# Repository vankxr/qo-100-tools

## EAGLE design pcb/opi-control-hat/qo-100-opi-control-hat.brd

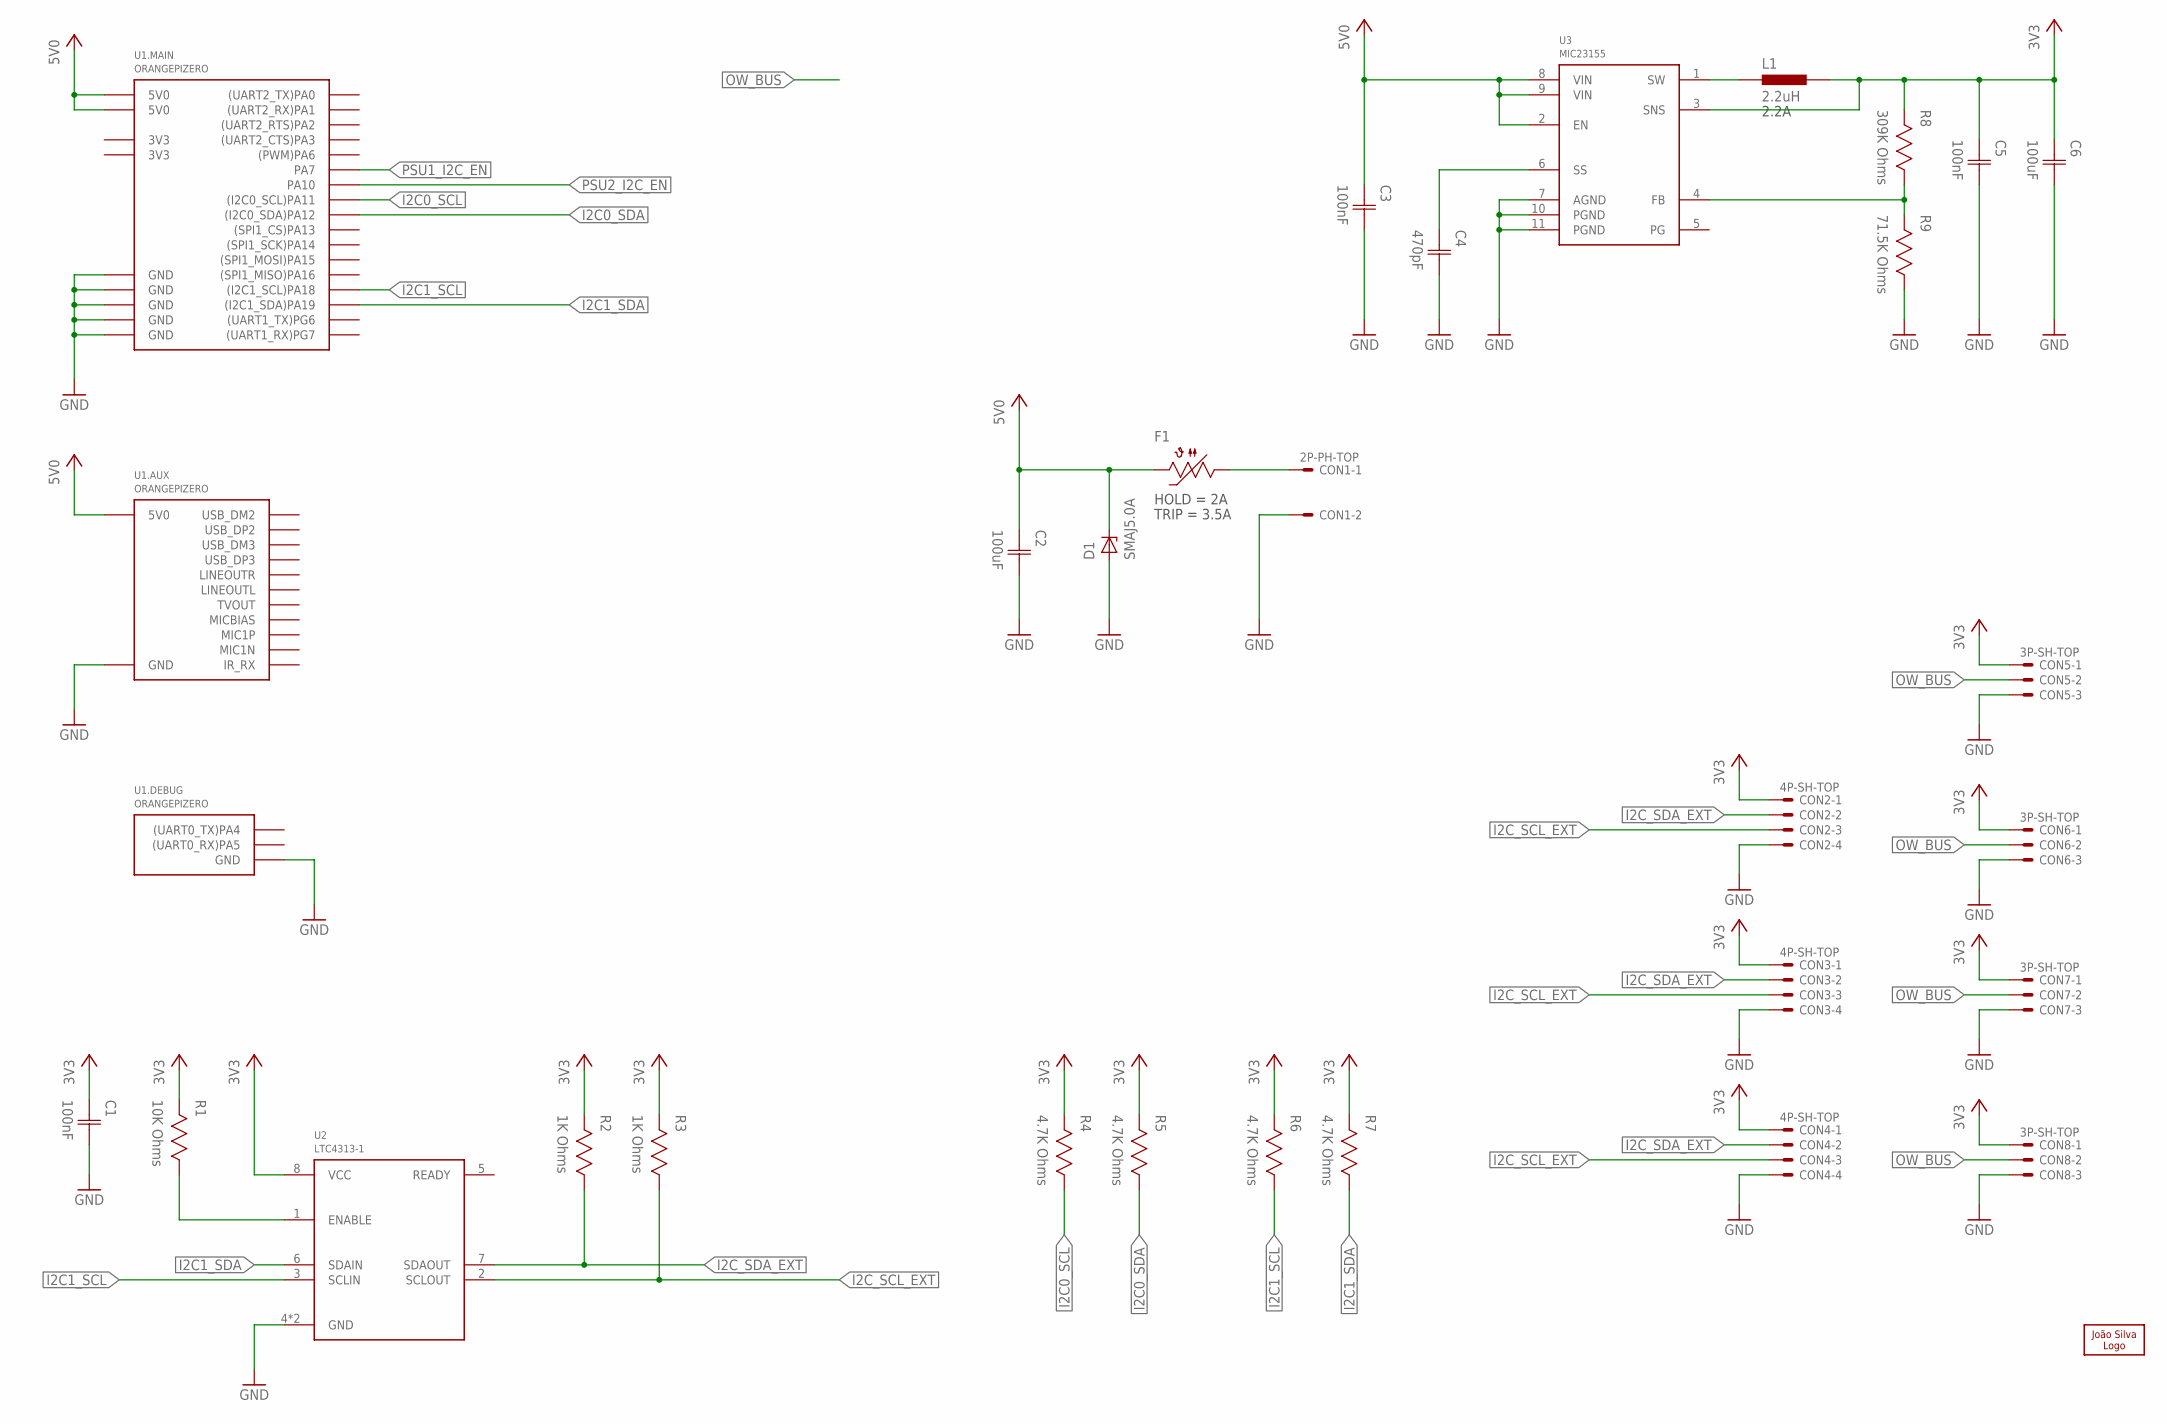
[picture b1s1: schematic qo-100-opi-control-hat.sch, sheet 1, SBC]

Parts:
C1, C3, C5: 100nF; CAP0603
C2, C6: 100uF; CAP1206
C4: 470pF; CAP0603
CON1: 2P-PH-TOP; PH-02-TOP
CON2, CON3, CON4: 4P-SH-TOP; SH-04-TOP
CON5, CON6, CON7, CON8: 3P-SH-TOP; SH-03-TOP
D1: SMAJ5.0A; DO214AC
F1: PTC1206; 1206
L1: 2.2uH; IND2520
LOGO1: JS-5MM; JS_5MM
R1: 10K Ohms; RES0603
R2, R3: 1K Ohms; RES0603
R4, R5, R6, R7: 4.7K Ohms; RES0603
R8: 309K Ohms; RES0603
R9: 71.5K Ohms; RES0603
U1: ORANGEPIZERO
U2: LTC4313-1; DFN8
U3: MIC23155; DFN10

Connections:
3V3: C1.1 (C1), C5.1 (C1), C6.1 (C1), CON2.1, CON3.1, CON4.1, CON5.1, CON6.1, CON7.1, CON8.1, L1.2, R1.2, R2.2, R3.2, R4.2, R5.2, R6.2, R7.2, R8.2, U2.8 (VCC), U3.3 (SNS); also elsewhere on the board
3V3_FB: R8.1, R9.2, U3.4 (FB)
3V3_SOFTSTART: C4.1 (C1), U3.6 (SS)
3V3_SW: L1.1, U3.1 (SW)
5V0: C2.1 (C1), C3.1 (C1), D1.C, F1.2, U1.MH$2 (5V0), U1.MH$4 (5V0), U1.SH$1 (5V0), U3.2 (EN), U3.8 (VIN), U3.9 (VIN)
GND: C1.2 (C2), C2.2 (C2), C3.2 (C2), C4.2 (C2), C5.2 (C2), C6.2 (C2), CON1.2, CON2.4, CON3.4, CON4.4, CON5.3, CON6.3, CON7.3, CON8.3, D1.A, R9.1, U1.DBG$1 (GND), U1.MH$6 (GND), U1.MH$9 (GND), U1.MH$14 (GND), U1.MH$20 (GND), U1.MH$25 (GND), U1.SH$2 (GND), U2.4 (GND), U2.9 (GND), U3.7 (AGND), U3.10 (PGND), U3.11 (PGND); also elsewhere on the board
I2C0_SCL: R4.1, U1.MH$5 ((I2C0_SCL)PA11); also elsewhere on the board
I2C0_SDA: R5.1, U1.MH$3 ((I2C0_SDA)PA12); also elsewhere on the board
I2C1_SCL: R6.1, U1.MH$18 ((I2C1_SCL)PA18), U2.3 (SCLIN)
I2C1_SDA: R7.1, U1.MH$16 ((I2C1_SDA)PA19), U2.6 (SDAIN)
I2C_SCL_EXT: CON2.3, CON3.3, CON4.3, R3.1, U2.2 (SCLOUT)
I2C_SDA_EXT: CON2.2, CON3.2, CON4.2, R2.1, U2.7 (SDAOUT)
unnamed: CON1.1, F1.1
unnamed: R1.1, U2.1 (ENABLE)
OW_BUS: CON5.2, CON6.2, CON7.2, CON8.2
PSU1_I2C_EN: U1.MH$12 (PA7); also elsewhere on the board
PSU2_I2C_EN: U1.MH$26 (PA10); also elsewhere on the board

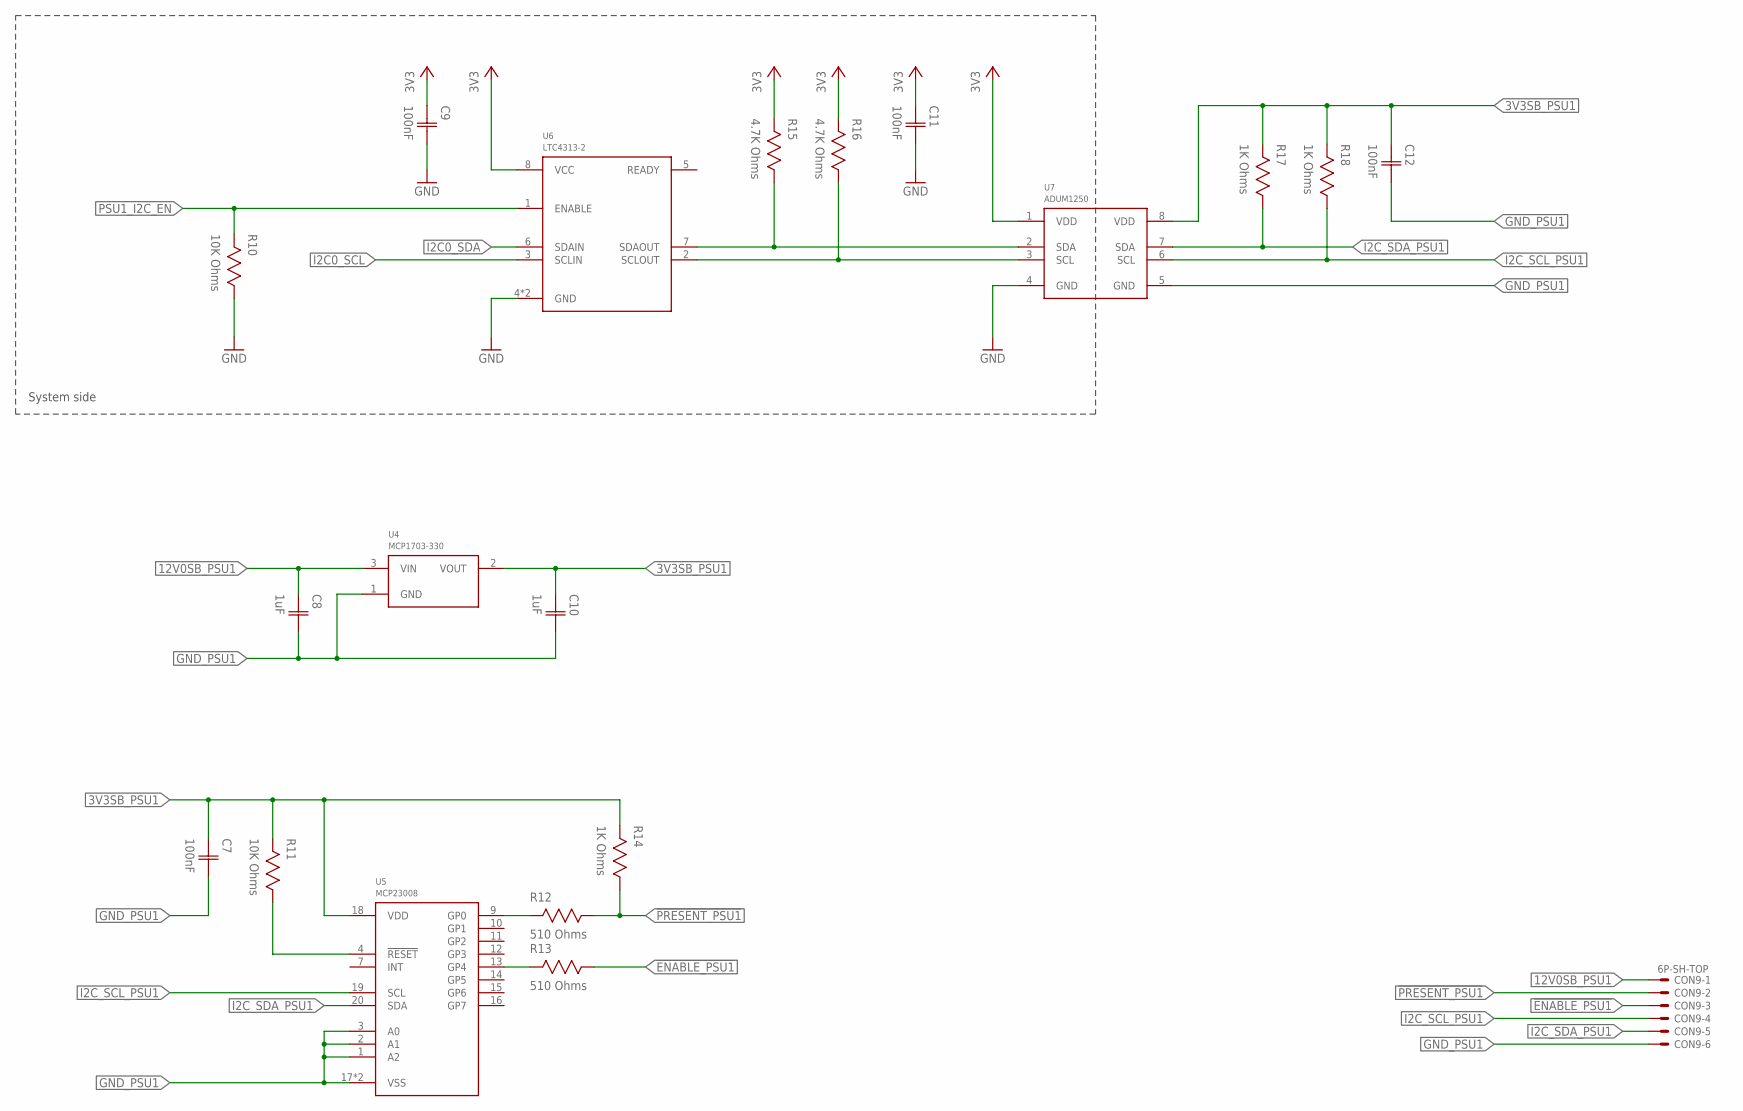
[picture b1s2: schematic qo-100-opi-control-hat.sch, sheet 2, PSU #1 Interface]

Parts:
C7, C9, C11, C12: 100nF; CAP0603
C8, C10: 1uF; CAP0603
CON9: 6P-SH-TOP; SH-06-TOP
R10, R11: 10K Ohms; RES0603
R12, R13: 510 Ohms; RES0603
R14, R17, R18: 1K Ohms; RES0603
R15, R16: 4.7K Ohms; RES0603
U4: MCP1703-330; SOT23
U5: MCP23008; QFN20
U6: LTC4313-2; DFN8
U7: ADUM1250; SOIC8

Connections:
3V3: C9.1 (C1), C11.1 (C1), R15.2, R16.2, U6.8 (VCC), U7.1 (VDD); also elsewhere on the board
3V3SB_PSU1: C7.1 (C1), C10.1 (C1), C12.1 (C1), R11.2, R14.2, R17.2, R18.2, U4.2 (VOUT), U5.18 (VDD), U7.8 (VDD)
12V0SB_PSU1: C8.1 (C1), CON9.1, U4.3 (VIN)
!ENABLE_PSU1: CON9.3, R13.1
!PRESENT_PSU1: CON9.2, R12.1, R14.1
GND: C9.2 (C2), C11.2 (C2), R10.1, U6.4 (GND), U6.9 (GND), U7.4 (GND); also elsewhere on the board
GND_PSU1: C7.2 (C2), C8.2 (C2), C10.2 (C2), C12.2 (C2), CON9.6, U4.1 (GND), U5.1 (A2), U5.2 (A1), U5.3 (A0), U5.17 (VSS), U5.PAD (VSS), U7.5 (GND)
I2C0_SCL: U6.3 (SCLIN); also elsewhere on the board
I2C0_SDA: U6.6 (SDAIN); also elsewhere on the board
I2C_SCL_PSU1: CON9.4, R18.1, U5.19 (SCL), U7.6 (SCL)
I2C_SDA_PSU1: CON9.5, R17.1, U5.20 (SDA), U7.7 (SDA)
unnamed: R16.1, U6.2 (SCLOUT), U7.3 (SCL)
unnamed: R15.1, U6.7 (SDAOUT), U7.2 (SDA)
unnamed: R11.1, U5.4 (!RESET)
unnamed: R13.2, U5.13 (GP4)
unnamed: R12.2, U5.9 (GP0)
PSU1_I2C_EN: R10.2, U6.1 (ENABLE); also elsewhere on the board

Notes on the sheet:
System side

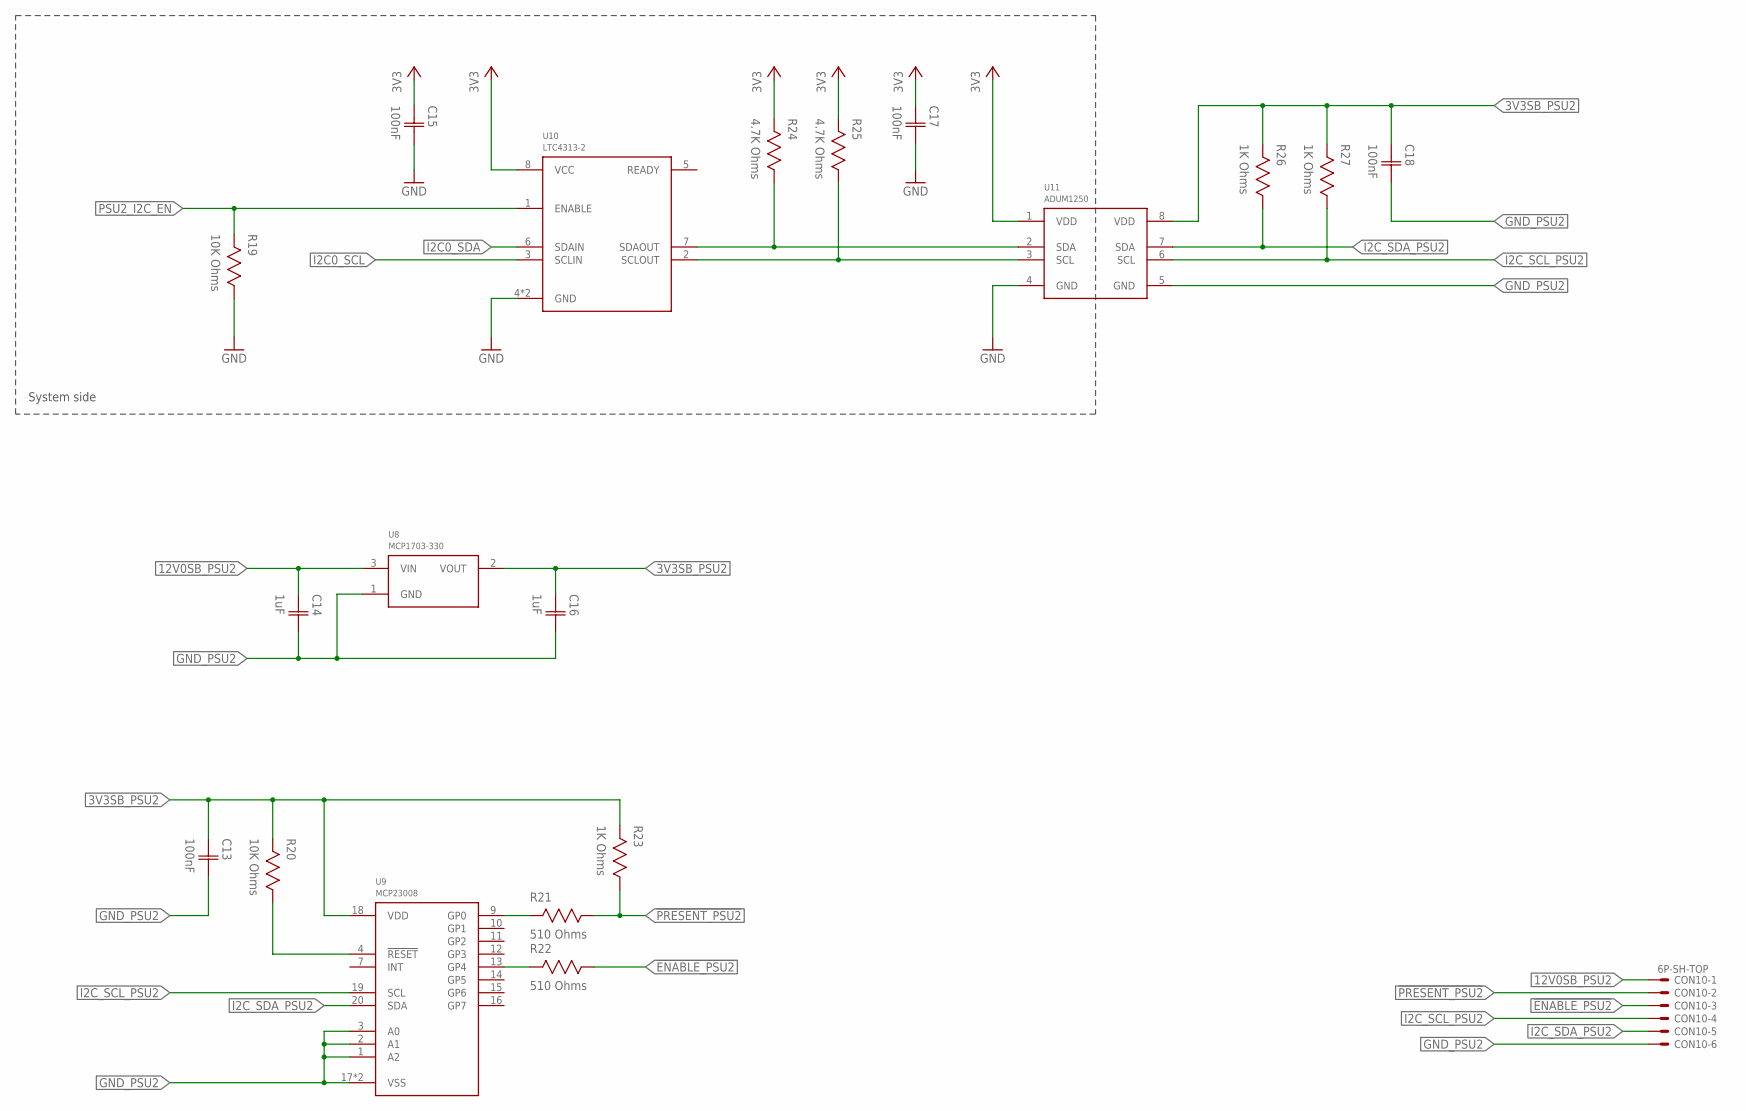
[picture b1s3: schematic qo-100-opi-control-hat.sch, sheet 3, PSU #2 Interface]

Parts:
C13, C15, C17, C18: 100nF; CAP0603
C14, C16: 1uF; CAP0603
CON10: 6P-SH-TOP; SH-06-TOP
R19, R20: 10K Ohms; RES0603
R21, R22: 510 Ohms; RES0603
R23, R26, R27: 1K Ohms; RES0603
R24, R25: 4.7K Ohms; RES0603
U8: MCP1703-330; SOT23
U9: MCP23008; QFN20
U10: LTC4313-2; DFN8
U11: ADUM1250; SOIC8

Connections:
3V3: C15.1 (C1), C17.1 (C1), R24.2, R25.2, U10.8 (VCC), U11.1 (VDD); also elsewhere on the board
3V3SB_PSU2: C13.1 (C1), C16.1 (C1), C18.1 (C1), R20.2, R23.2, R26.2, R27.2, U8.2 (VOUT), U9.18 (VDD), U11.8 (VDD)
12V0SB_PSU2: C14.1 (C1), CON10.1, U8.3 (VIN)
!ENABLE_PSU2: CON10.3, R22.1
!PRESENT_PSU2: CON10.2, R21.1, R23.1
GND: C15.2 (C2), C17.2 (C2), R19.1, U10.4 (GND), U10.9 (GND), U11.4 (GND); also elsewhere on the board
GND_PSU2: C13.2 (C2), C14.2 (C2), C16.2 (C2), C18.2 (C2), CON10.6, U8.1 (GND), U9.1 (A2), U9.2 (A1), U9.3 (A0), U9.17 (VSS), U9.PAD (VSS), U11.5 (GND)
I2C0_SCL: U10.3 (SCLIN); also elsewhere on the board
I2C0_SDA: U10.6 (SDAIN); also elsewhere on the board
I2C_SCL_PSU2: CON10.4, R27.1, U9.19 (SCL), U11.6 (SCL)
I2C_SDA_PSU2: CON10.5, R26.1, U9.20 (SDA), U11.7 (SDA)
unnamed: R25.1, U10.2 (SCLOUT), U11.3 (SCL)
unnamed: R24.1, U10.7 (SDAOUT), U11.2 (SDA)
unnamed: R20.1, U9.4 (!RESET)
unnamed: R22.2, U9.13 (GP4)
unnamed: R21.2, U9.9 (GP0)
PSU2_I2C_EN: R19.2, U10.1 (ENABLE); also elsewhere on the board

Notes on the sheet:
System side

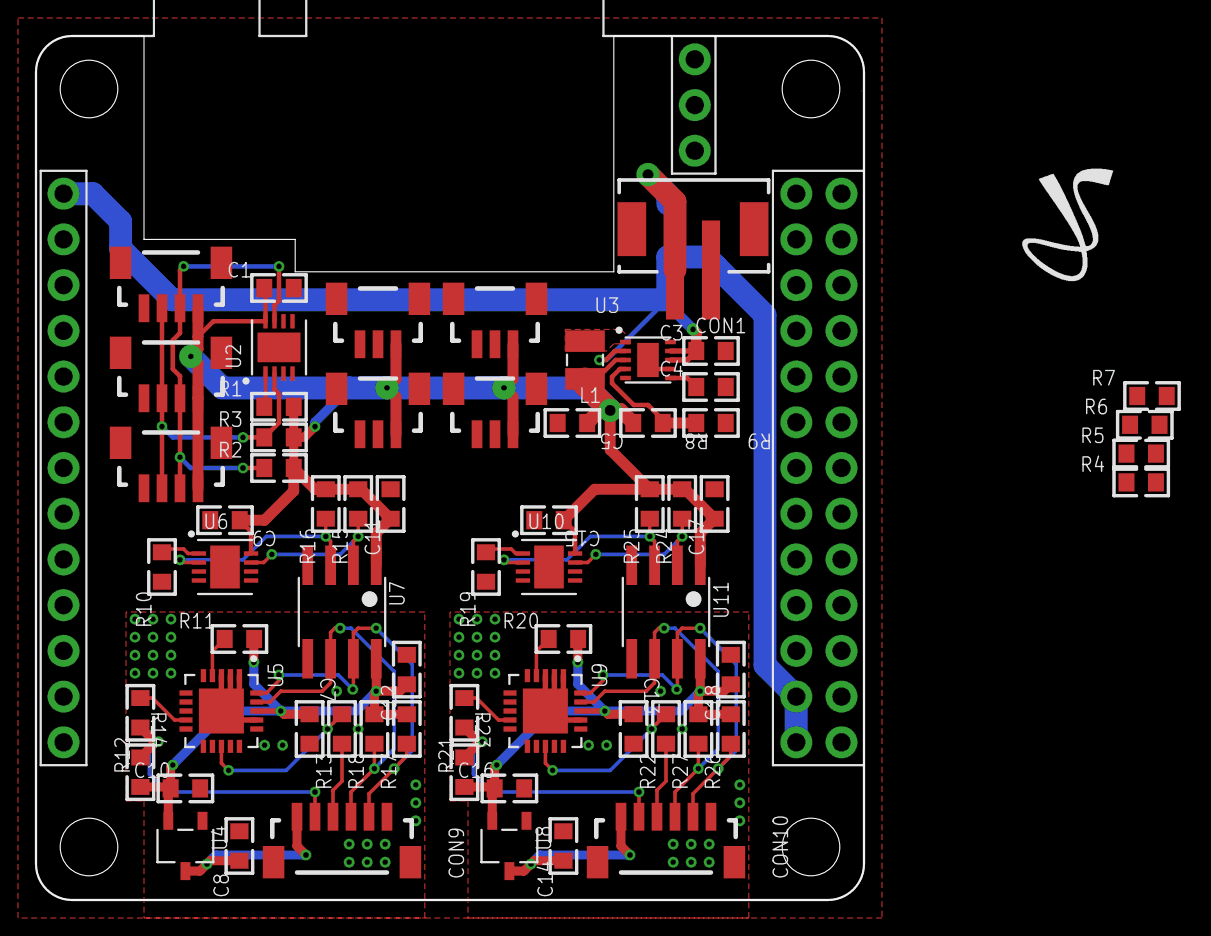
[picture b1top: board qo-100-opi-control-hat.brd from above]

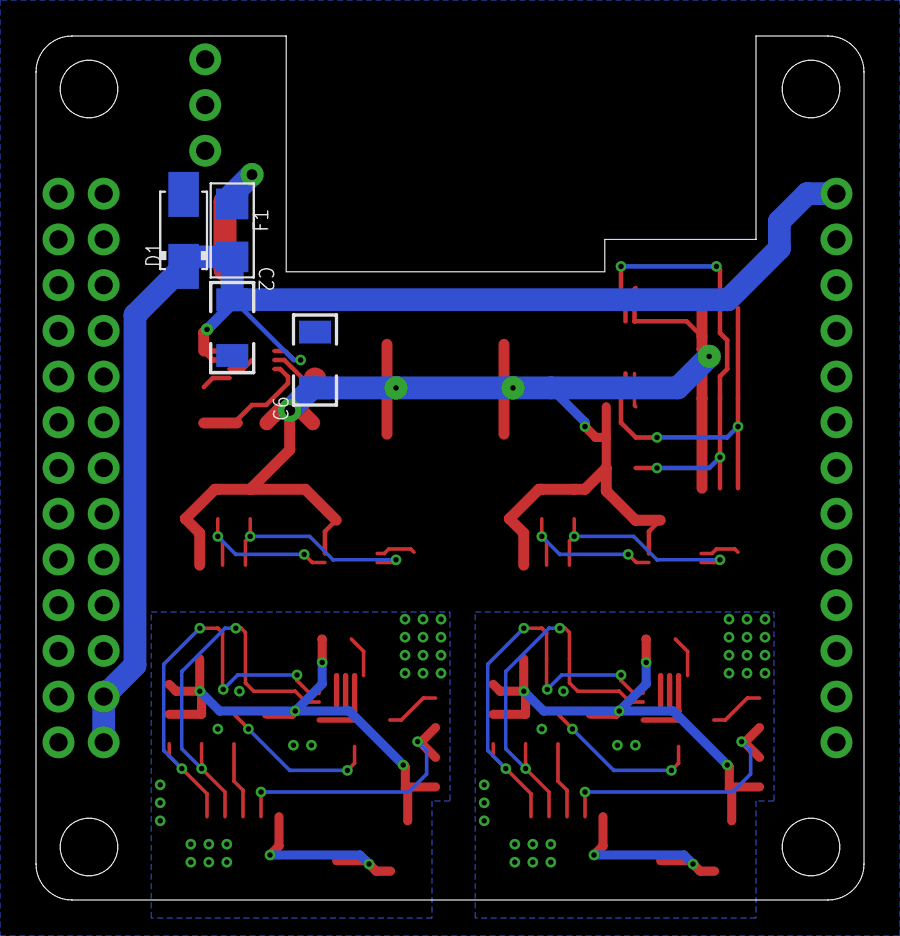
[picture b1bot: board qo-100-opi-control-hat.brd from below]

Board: 2 copper layers, 46.0 x 48.0 mm, 70 parts (4 on the bottom side), 41 nets.

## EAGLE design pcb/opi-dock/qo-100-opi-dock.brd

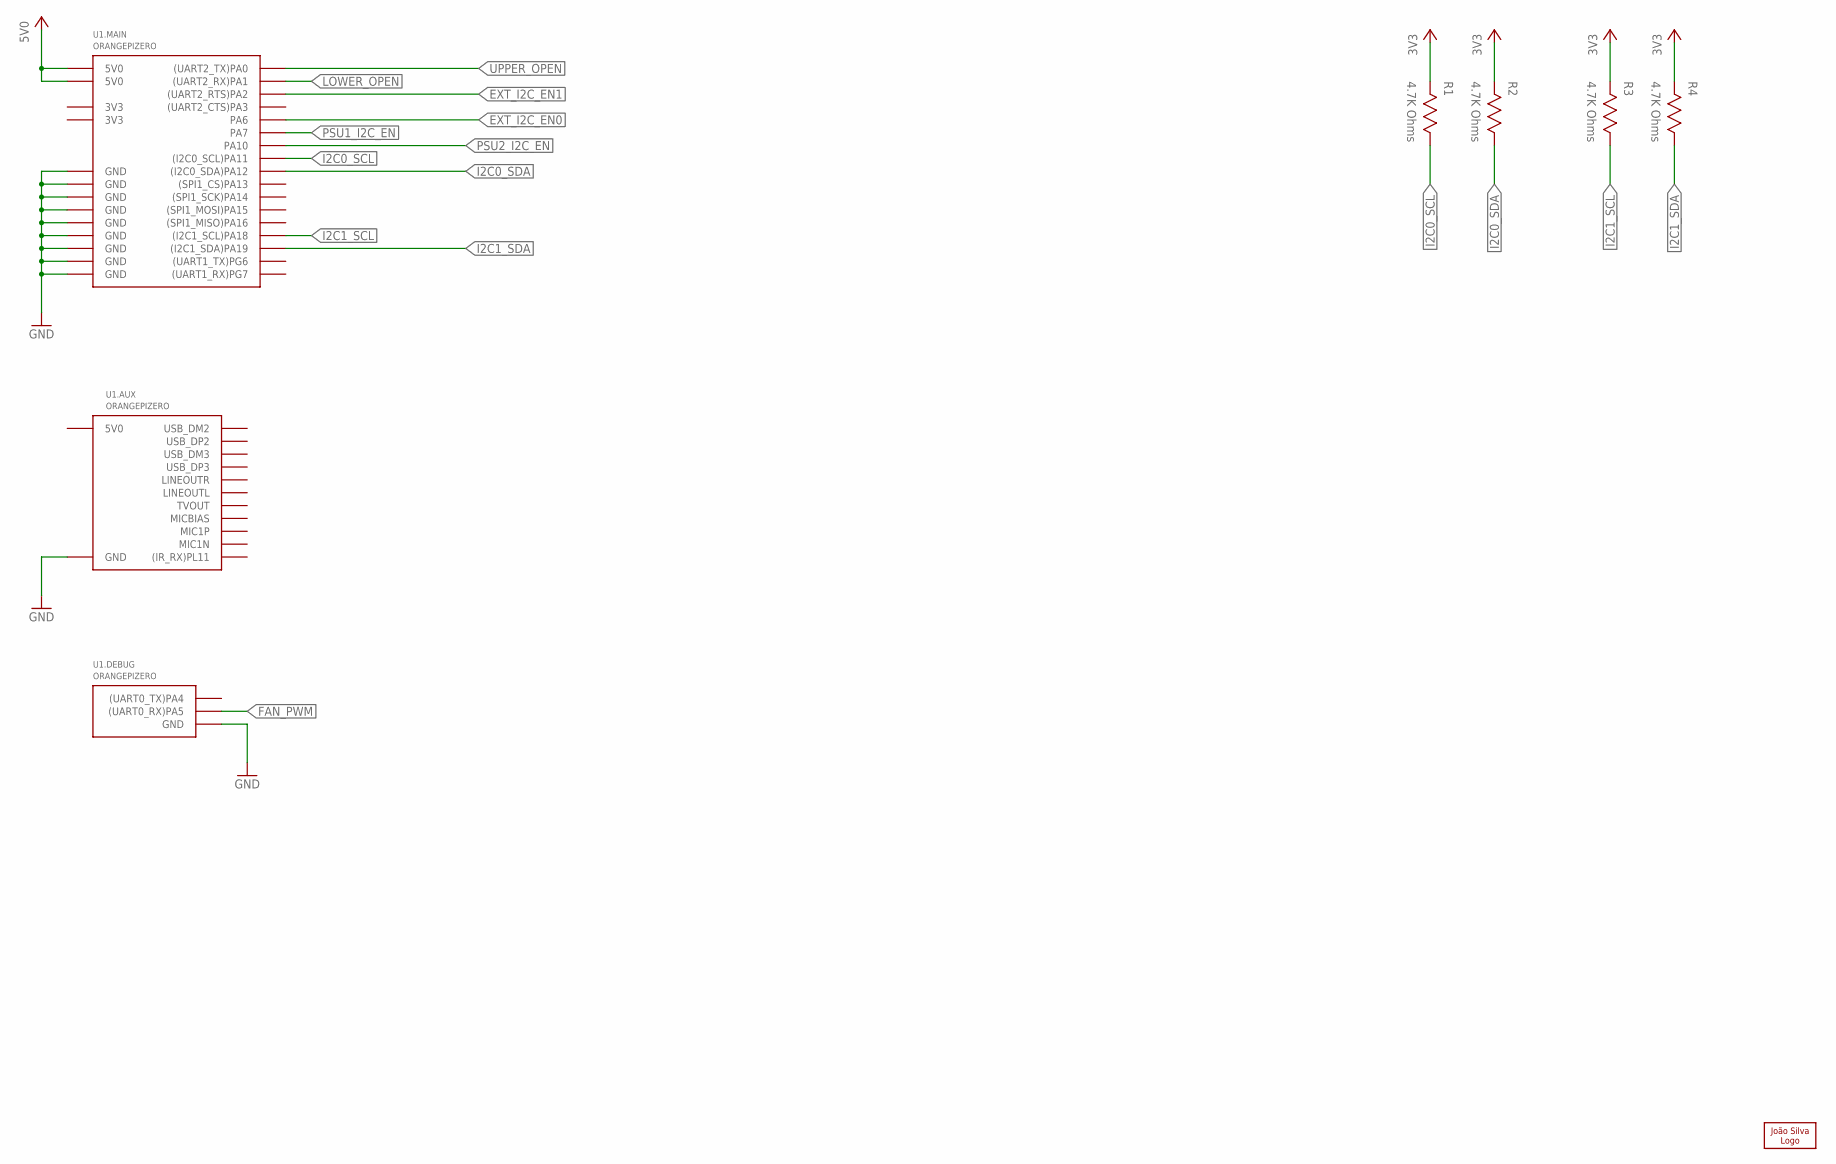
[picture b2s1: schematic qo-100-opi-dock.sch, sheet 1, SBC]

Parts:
LOGO1: JS-5MM; JS_5MM
R1, R2, R3, R4: 4.7K Ohms; RES0603
U1: ORANGEPIZERO

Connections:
3V3: R1.2, R2.2, R3.2, R4.2; also elsewhere on the board
5V0: U1.MH$2 (5V0), U1.MH$4 (5V0); also elsewhere on the board
EXT_I2C_EN0: U1.MH$7 (PA6); also elsewhere on the board
EXT_I2C_EN1: U1.MH$22 ((UART2_RTS)PA2); also elsewhere on the board
FAN_PWM: U1.DBG$2 ((UART0_RX)PA5); also elsewhere on the board
GND: U1.DBG$1 (GND), U1.GND@0 (GND), U1.GND@1 (GND), U1.GND@2 (GND), U1.GND@3 (GND), U1.MH$6 (GND), U1.MH$9 (GND), U1.MH$14 (GND), U1.MH$20 (GND), U1.MH$25 (GND), U1.SH$2 (GND); also elsewhere on the board
I2C0_SCL: R1.1, U1.MH$5 ((I2C0_SCL)PA11); also elsewhere on the board
I2C0_SDA: R2.1, U1.MH$3 ((I2C0_SDA)PA12); also elsewhere on the board
I2C1_SCL: R3.1, U1.MH$18 ((I2C1_SCL)PA18); also elsewhere on the board
I2C1_SDA: R4.1, U1.MH$16 ((I2C1_SDA)PA19); also elsewhere on the board
LOWER_OPEN: U1.MH$11 ((UART2_RX)PA1); also elsewhere on the board
PSU1_I2C_EN: U1.MH$12 (PA7); also elsewhere on the board
PSU2_I2C_EN: U1.MH$26 (PA10); also elsewhere on the board
UPPER_OPEN: U1.MH$13 ((UART2_TX)PA0); also elsewhere on the board

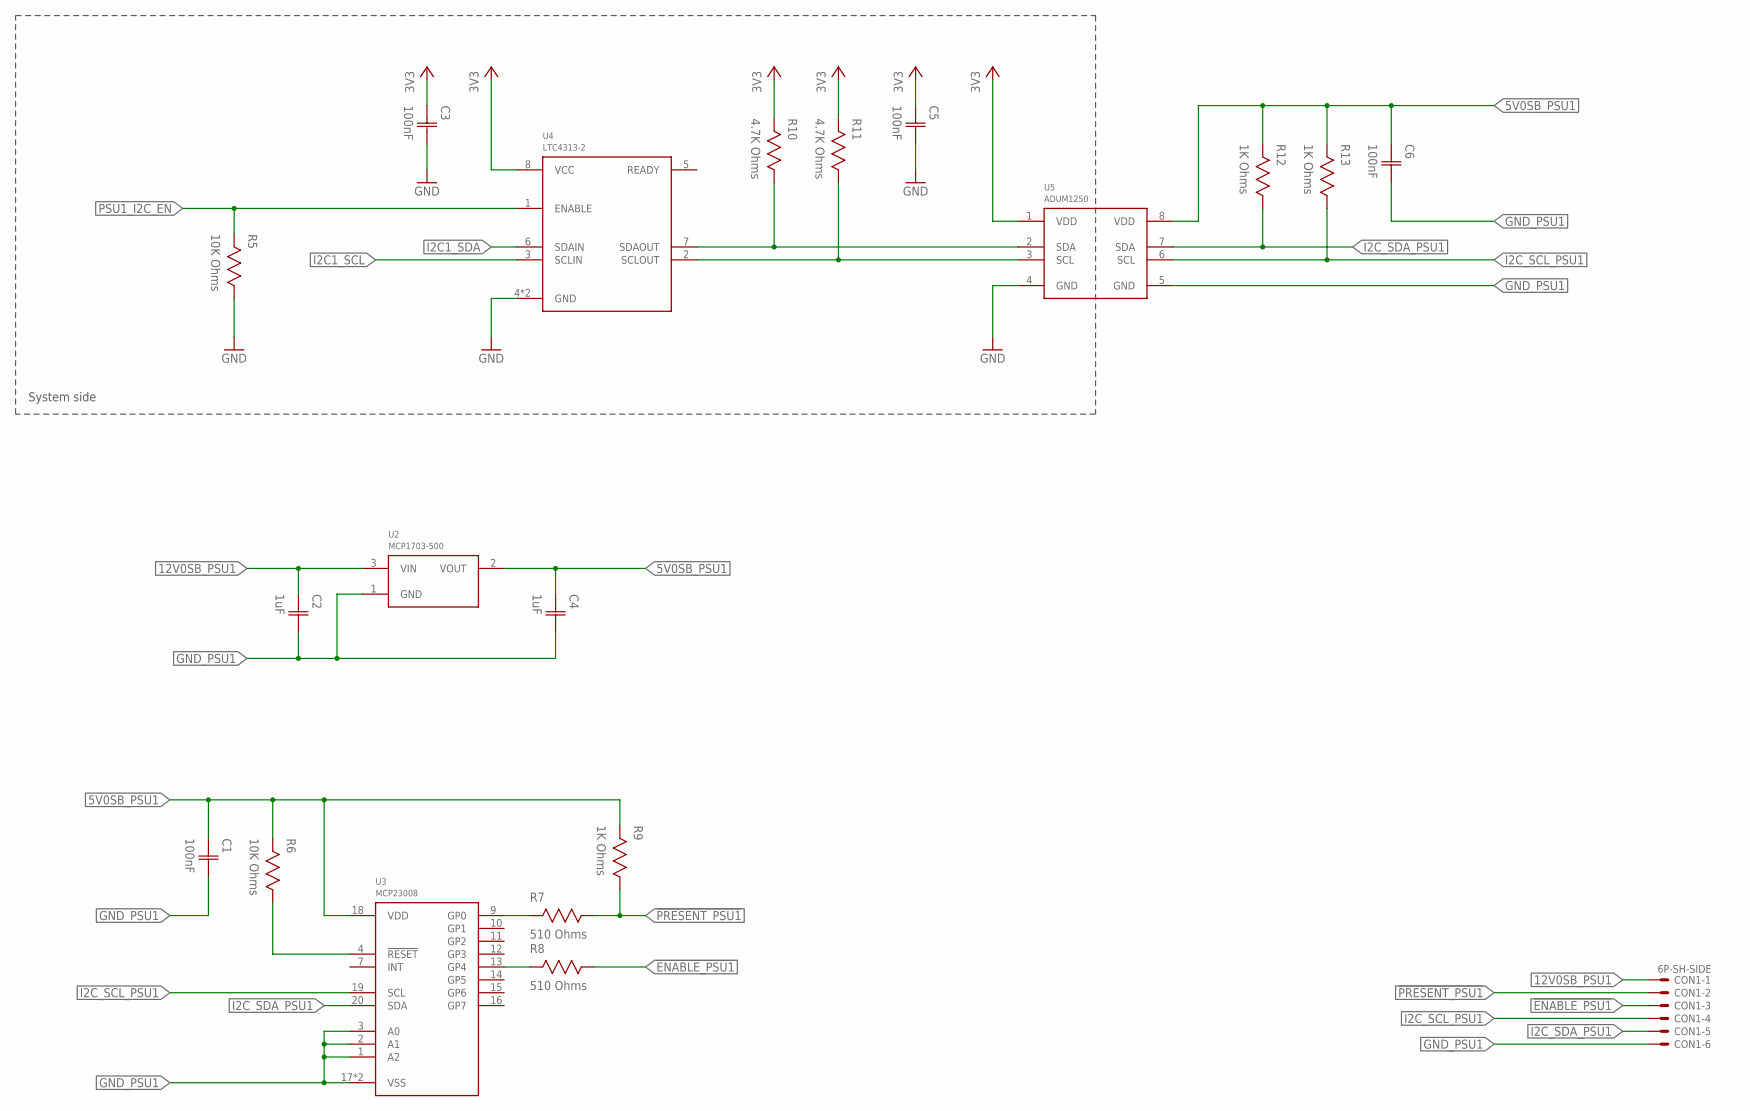
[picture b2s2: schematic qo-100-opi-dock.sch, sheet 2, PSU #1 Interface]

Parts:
C1, C3, C5, C6: 100nF; CAP0603
C2, C4: 1uF; CAP0603
CON1: 6P-SH-SIDE; SH-06-SIDE
R5, R6: 10K Ohms; RES0603
R7, R8: 510 Ohms; RES0603
R9, R12, R13: 1K Ohms; RES0603
R10, R11: 4.7K Ohms; RES0603
U2: MCP1703-500; SOT23
U3: MCP23008; QFN20
U4: LTC4313-2; DFN8
U5: ADUM1250; SOIC8

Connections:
3V3: C3.1 (C1), C5.1 (C1), R10.2, R11.2, U4.8 (VCC), U5.1 (VDD); also elsewhere on the board
5V0SB_PSU1: C1.1 (C1), C4.1 (C1), C6.1 (C1), R6.2, R9.2, R12.2, R13.2, U2.2 (VOUT), U3.18 (VDD), U5.8 (VDD)
12V0SB_PSU1: C2.1 (C1), CON1.1, U2.3 (VIN)
!ENABLE_PSU1: CON1.3, R8.1
!PRESENT_PSU1: CON1.2, R7.1, R9.1
GND: C3.2 (C2), C5.2 (C2), R5.1, U4.4 (GND), U4.9 (GND), U5.4 (GND); also elsewhere on the board
GND_PSU1: C1.2 (C2), C2.2 (C2), C4.2 (C2), C6.2 (C2), CON1.6, U2.1 (GND), U3.1 (A2), U3.2 (A1), U3.3 (A0), U3.17 (VSS), U3.PAD (VSS), U5.5 (GND)
I2C1_SCL: U4.3 (SCLIN); also elsewhere on the board
I2C1_SDA: U4.6 (SDAIN); also elsewhere on the board
I2C_SCL_PSU1: CON1.4, R13.1, U3.19 (SCL), U5.6 (SCL)
I2C_SDA_PSU1: CON1.5, R12.1, U3.20 (SDA), U5.7 (SDA)
unnamed: R11.1, U4.2 (SCLOUT), U5.3 (SCL)
unnamed: R10.1, U4.7 (SDAOUT), U5.2 (SDA)
unnamed: R6.1, U3.4 (!RESET)
unnamed: R8.2, U3.13 (GP4)
unnamed: R7.2, U3.9 (GP0)
PSU1_I2C_EN: R5.2, U4.1 (ENABLE); also elsewhere on the board

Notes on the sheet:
System side

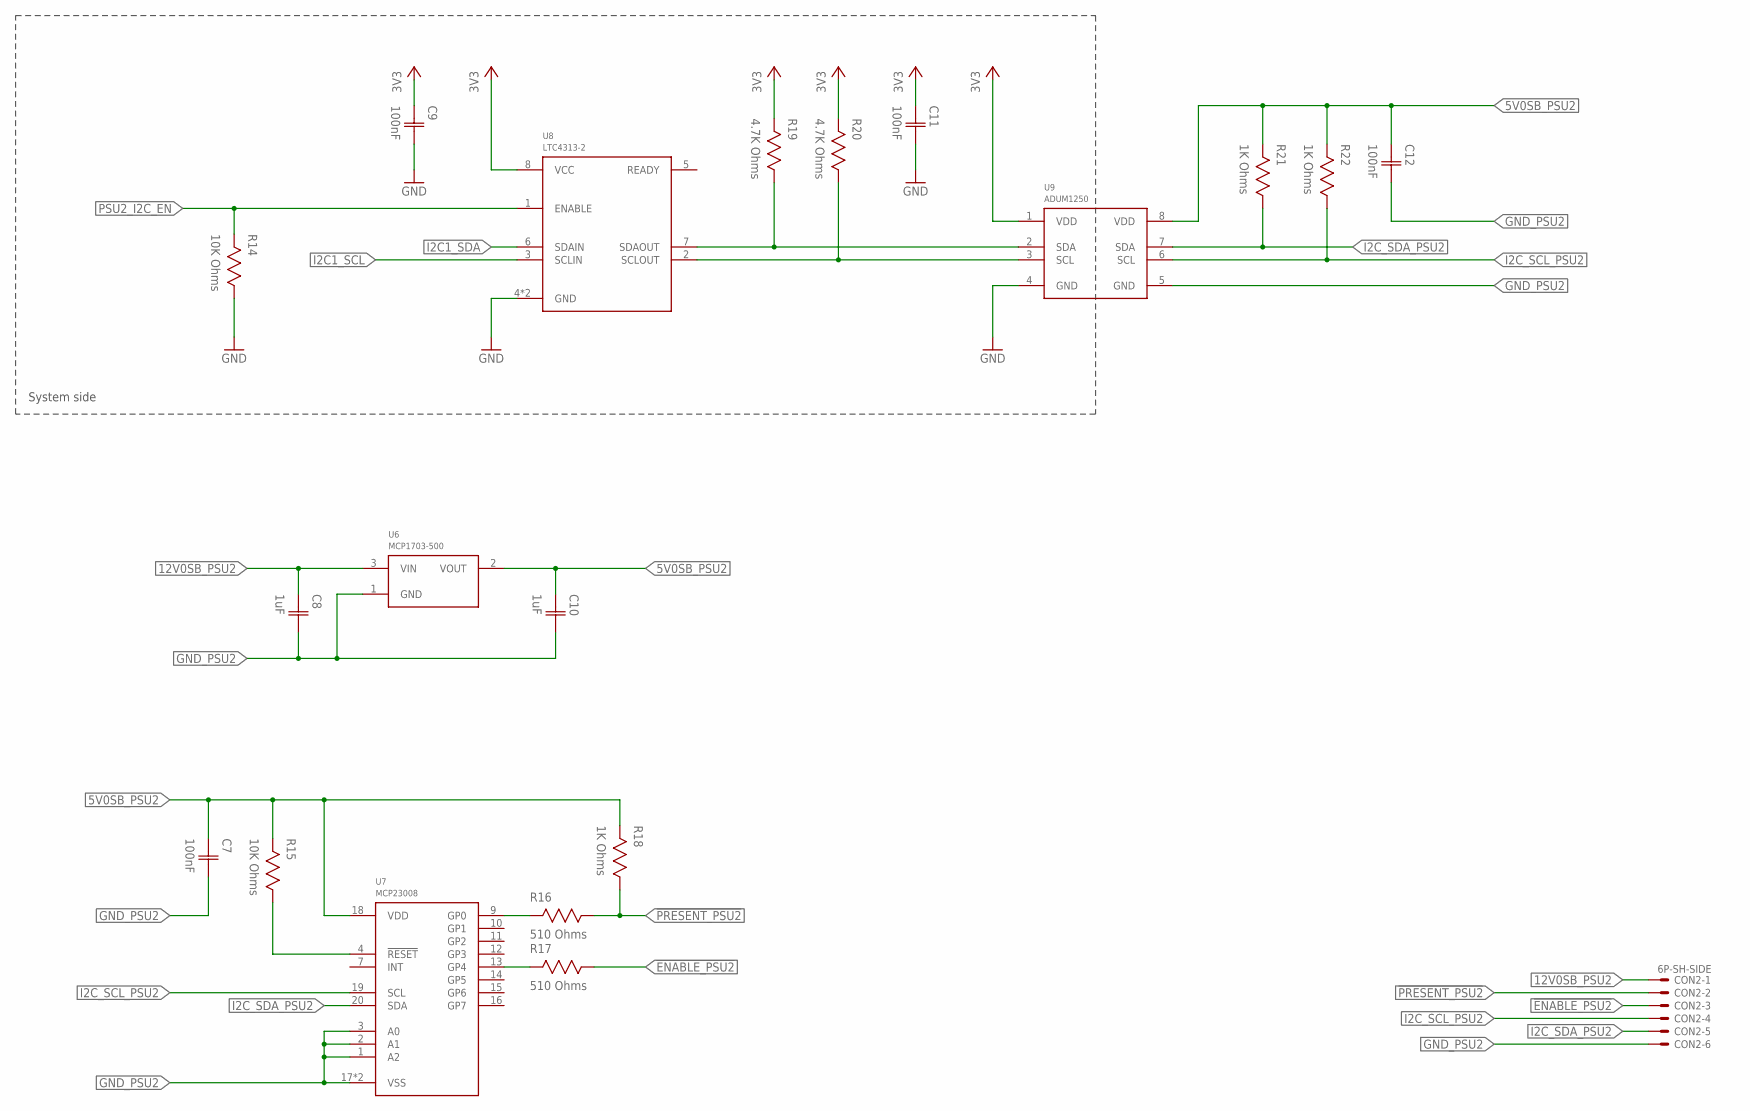
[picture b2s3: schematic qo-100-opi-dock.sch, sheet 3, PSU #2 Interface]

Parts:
C7, C9, C11, C12: 100nF; CAP0603
C8, C10: 1uF; CAP0603
CON2: 6P-SH-SIDE; SH-06-SIDE
R14, R15: 10K Ohms; RES0603
R16, R17: 510 Ohms; RES0603
R18, R21, R22: 1K Ohms; RES0603
R19, R20: 4.7K Ohms; RES0603
U6: MCP1703-500; SOT23
U7: MCP23008; QFN20
U8: LTC4313-2; DFN8
U9: ADUM1250; SOIC8

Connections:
3V3: C9.1 (C1), C11.1 (C1), R19.2, R20.2, U8.8 (VCC), U9.1 (VDD); also elsewhere on the board
5V0SB_PSU2: C7.1 (C1), C10.1 (C1), C12.1 (C1), R15.2, R18.2, R21.2, R22.2, U6.2 (VOUT), U7.18 (VDD), U9.8 (VDD)
12V0SB_PSU2: C8.1 (C1), CON2.1, U6.3 (VIN)
!ENABLE_PSU2: CON2.3, R17.1
!PRESENT_PSU2: CON2.2, R16.1, R18.1
GND: C9.2 (C2), C11.2 (C2), R14.1, U8.4 (GND), U8.9 (GND), U9.4 (GND); also elsewhere on the board
GND_PSU2: C7.2 (C2), C8.2 (C2), C10.2 (C2), C12.2 (C2), CON2.6, U6.1 (GND), U7.1 (A2), U7.2 (A1), U7.3 (A0), U7.17 (VSS), U7.PAD (VSS), U9.5 (GND)
I2C1_SCL: U8.3 (SCLIN); also elsewhere on the board
I2C1_SDA: U8.6 (SDAIN); also elsewhere on the board
I2C_SCL_PSU2: CON2.4, R22.1, U7.19 (SCL), U9.6 (SCL)
I2C_SDA_PSU2: CON2.5, R21.1, U7.20 (SDA), U9.7 (SDA)
unnamed: R20.1, U8.2 (SCLOUT), U9.3 (SCL)
unnamed: R19.1, U8.7 (SDAOUT), U9.2 (SDA)
unnamed: R15.1, U7.4 (!RESET)
unnamed: R17.2, U7.13 (GP4)
unnamed: R16.2, U7.9 (GP0)
PSU2_I2C_EN: R14.2, U8.1 (ENABLE); also elsewhere on the board

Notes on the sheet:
System side
